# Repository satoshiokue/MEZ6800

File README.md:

# MEZ6800
6800 Mezzanine board for EMUZ80  

C1 = 0.1uF

https://github.com/satoshiokue/EMUZ80-6800

MEZ6800専用プリント基板 - オレンジピコショップ  
https://store.shopping.yahoo.co.jp/orangepicoshop/pico-a-059.html

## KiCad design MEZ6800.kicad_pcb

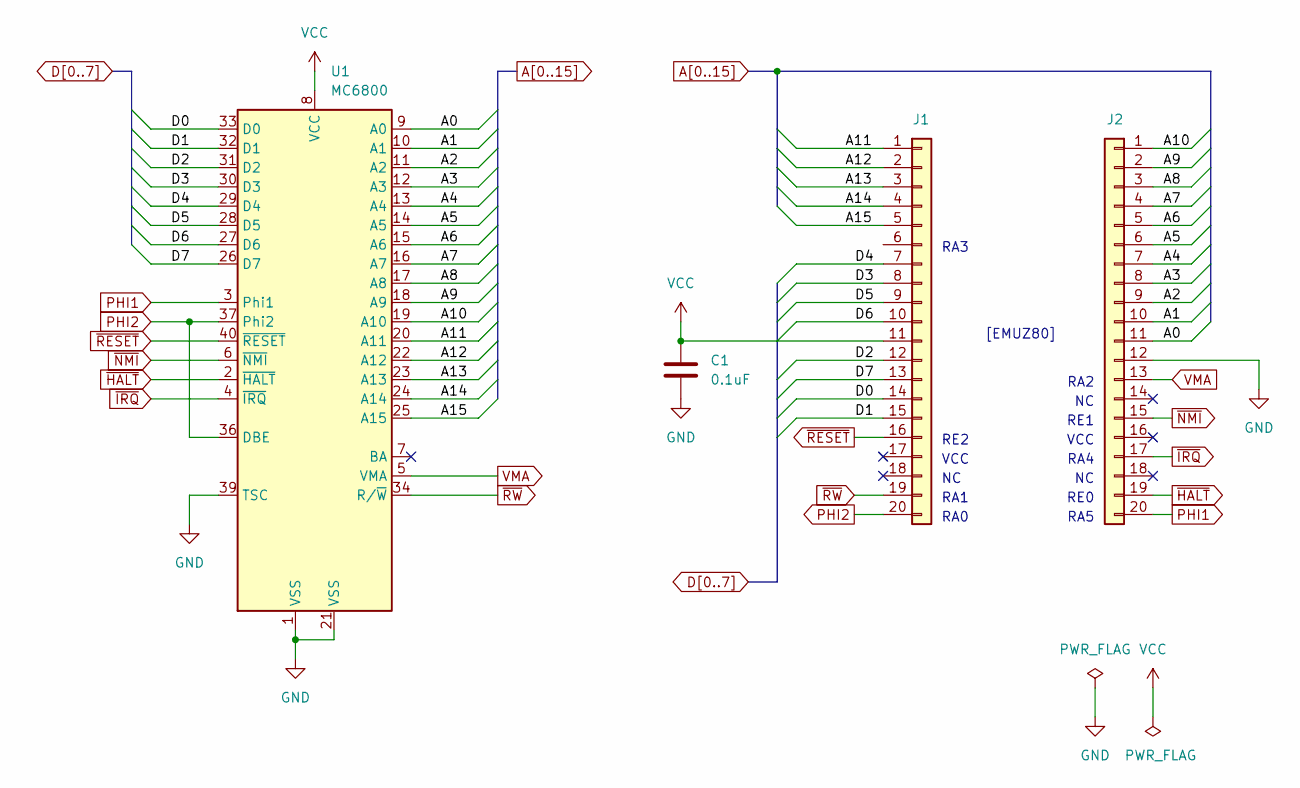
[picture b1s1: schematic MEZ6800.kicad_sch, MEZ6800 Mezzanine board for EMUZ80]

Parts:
C1: 0.1uF; C_Disc_D3.8mm_W2.6mm_P2.50mm
J1, J2: Conn_01x20; PinHeader_1x20_P2.54mm_Vertical
U1: MC6800; DIP-40_W15.24mm

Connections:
A0: J2.11, U1.9 (A0)
A1: J2.10, U1.10 (A1)
A2: J2.9, U1.11 (A2)
A3: J2.8, U1.12 (A3)
A4: J2.7, U1.13 (A4)
A5: J2.6, U1.14 (A5)
A6: J2.5, U1.15 (A6)
A7: J2.4, U1.16 (A7)
A8: J2.3, U1.17 (A8)
A9: J2.2, U1.18 (A9)
A10: J2.1, U1.19 (A10)
A11: J1.1, U1.20 (A11)
A12: J1.2, U1.22 (A12)
A13: J1.3, U1.23 (A13)
A14: J1.4, U1.24 (A14)
A15: J1.5, U1.25 (A15)
D0: J1.14, U1.33 (D0)
D1: J1.15, U1.32 (D1)
D2: J1.12, U1.31 (D2)
D3: J1.8, U1.30 (D3)
D4: J1.7, U1.29 (D4)
D5: J1.9, U1.28 (D5)
D6: J1.10, U1.27 (D6)
D7: J1.13, U1.26 (D7)
GND: C1.2, J2.12, U1.1 (VSS), U1.21 (VSS), U1.39 (TSC)
PHI1: J2.20, U1.3 (Phi1)
PHI2: J1.20, U1.36 (DBE), U1.37 (Phi2)
VCC: C1.1, J1.11, U1.8 (VCC)
VMA: J2.13, U1.5 (VMA)
~HALT: J2.19, U1.2 (~HALT)
~IRQ: J2.17, U1.4 (~IRQ)
~NMI: J2.15, U1.6 (~NMI)
~RESET: J1.16, U1.40 (~RESET)
~RW: J1.19, U1.34 (R/~W)

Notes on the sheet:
RA2
[EMUZ80]
VCC
RA3
RE2
RA4
RA0
RE0
RA1
RE1
RA5

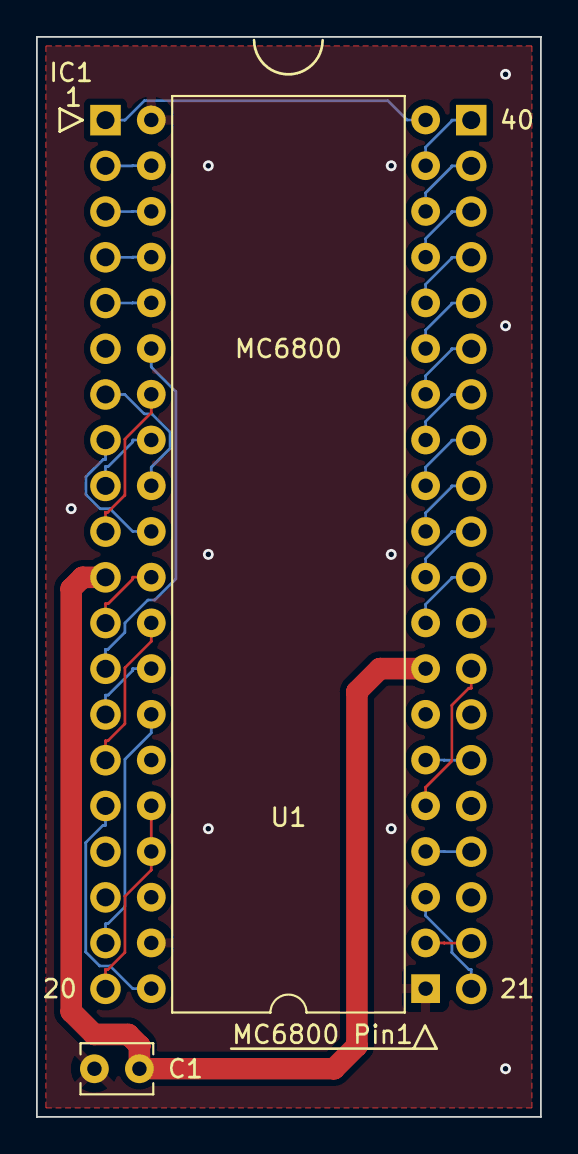
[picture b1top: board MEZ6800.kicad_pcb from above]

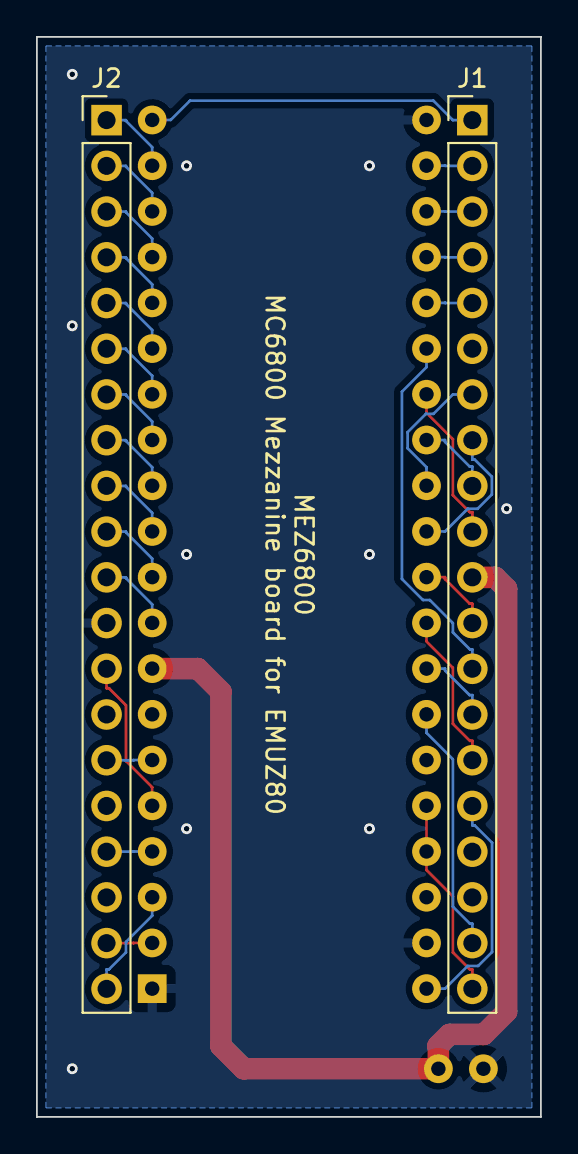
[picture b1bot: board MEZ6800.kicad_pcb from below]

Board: 2 copper layers, 28.0 x 60.0 mm, 4 parts (2 on the bottom side), 34 nets.

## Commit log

2022-09-09 Create foo
